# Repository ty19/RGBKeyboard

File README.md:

# RGBKeyboard
Custom RGB Keyboard PCB and Firmware project

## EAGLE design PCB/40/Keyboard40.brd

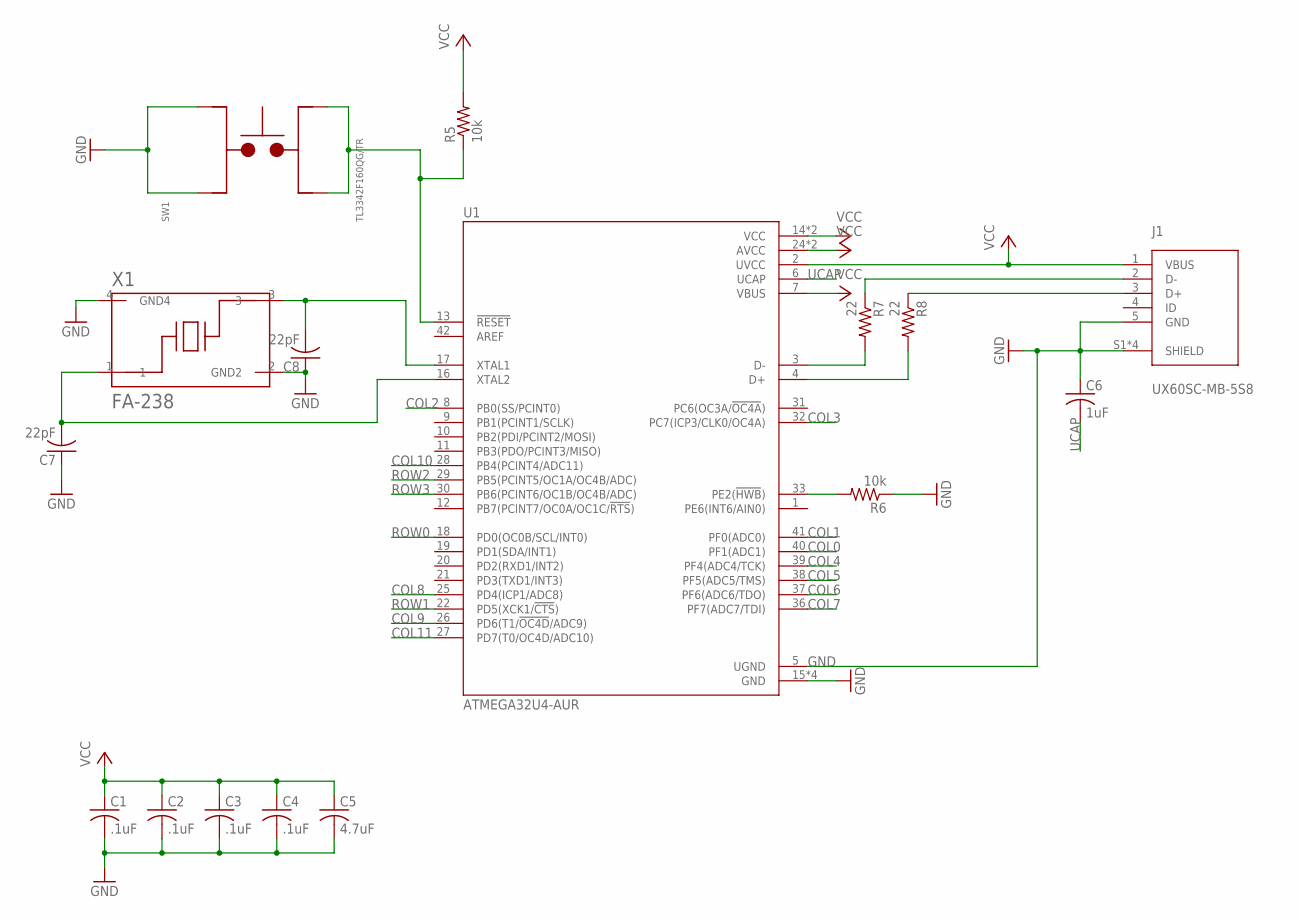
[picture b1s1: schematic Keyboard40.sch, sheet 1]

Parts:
C1, C2, C3, C4: .1uF; C0805
C5: 4.7uF; C0805
C6: 1uF; C0805
C7, C8: 22pF; C0805
J1: UX60SC-MB-5S8; HIROSE_UX60SC-MB-5S8
R5, R6: 10k; R0805
R7, R8: 22; R0805
SW1: TL3342F160QG/TR; SW_TL3342F160QG/TR
U1: ATMEGA32U4-AUR; QFP80P1200X1200X120-44N
X1: FA-238; OSCCC320X250X70-4N

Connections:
COL0: U1.40 (PF1(ADC1)); also elsewhere on the board
COL1: U1.41 (PF0(ADC0)); also elsewhere on the board
COL2: U1.8 (PB0(SS/PCINT0)); also elsewhere on the board
COL3: U1.32 (PC7(ICP3/CLK0/OC4A)); also elsewhere on the board
COL4: U1.39 (PF4(ADC4/TCK)); also elsewhere on the board
COL5: U1.38 (PF5(ADC5/TMS)); also elsewhere on the board
COL6: U1.37 (PF6(ADC6/TDO)); also elsewhere on the board
COL7: U1.36 (PF7(ADC7/TDI)); also elsewhere on the board
COL8: U1.25 (PD4(ICP1/ADC8)); also elsewhere on the board
COL9: U1.26 (PD6(T1/!OC4D!/ADC9)); also elsewhere on the board
COL10: U1.28 (PB4(PCINT4/ADC11)); also elsewhere on the board
COL11: U1.27 (PD7(T0/OC4D/ADC10)); also elsewhere on the board
GND: C1.2, C2.2, C3.2, C4.2, C5.2, C6.1, C7.1, C8.1, J1.5 (GND), J1.S1 (SHIELD), J1.S2 (SHIELD), J1.S3 (SHIELD), J1.S4 (SHIELD), R6.1, SW1.3, SW1.4, U1.5 (UGND), U1.15 (GND), U1.23 (GND), U1.35 (GND), U1.43 (GND), X1.2 (GND2), X1.4 (GND4)
unnamed: C8.2, U1.17 (XTAL1), X1.3
unnamed: C7.2, U1.16 (XTAL2), X1.1
unnamed: R5.1, SW1.1, SW1.2, U1.13 (!RESET)
unnamed: R6.2, U1.33 (PE2(!HWB!))
unnamed: R7.2, U1.3 (D-)
unnamed: J1.2 (D-), R7.1
unnamed: R8.2, U1.4 (D+)
unnamed: J1.3 (D+), R8.1
ROW0: U1.18 (PD0(OC0B/SCL/INT0)); also elsewhere on the board
ROW1: U1.22 (PD5(XCK1/!CTS!)); also elsewhere on the board
ROW2: U1.29 (PB5(PCINT5/OC1A/OC4B/ADC)); also elsewhere on the board
ROW3: U1.30 (PB6(PCINT6/OC1B/OC4B/ADC)); also elsewhere on the board
UCAP: C6.2, U1.6 (UCAP)
VCC: C1.1, C2.1, C3.1, C4.1, C5.1, J1.1 (VBUS), R5.2, U1.2 (UVCC), U1.7 (VBUS), U1.14 (VCC), U1.24 (AVCC), U1.34 (VCC), U1.44 (AVCC)

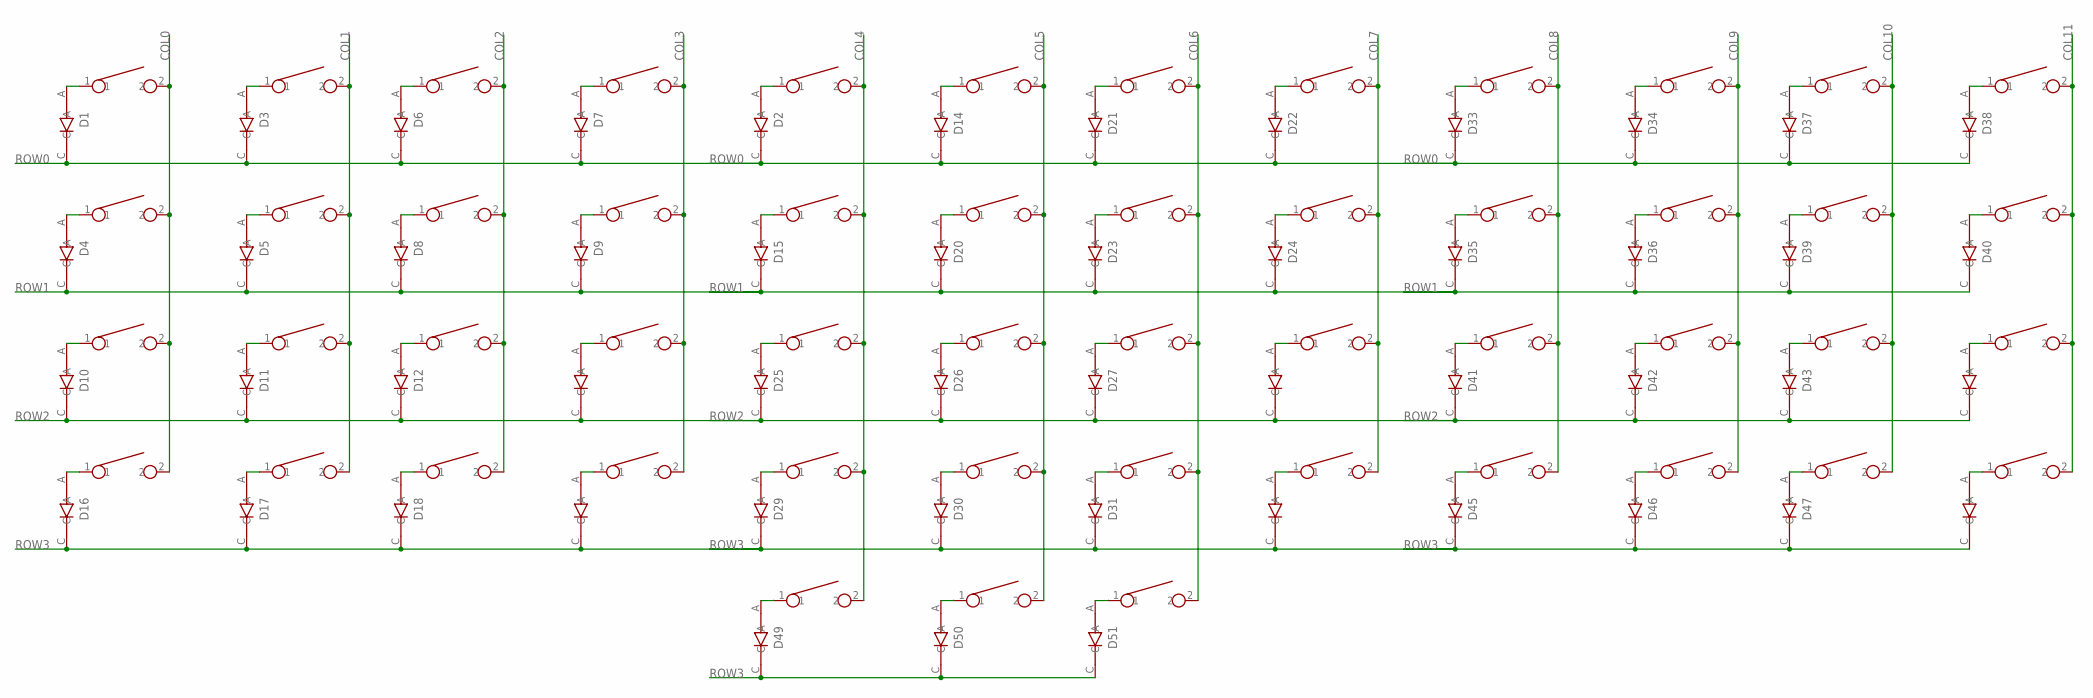
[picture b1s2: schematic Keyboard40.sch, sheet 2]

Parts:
D1, D2, D3, D4, D5, D6, D7, D8, D9, D10, D11, D12, D13, D14, D15, D16, D17, D18, D19, D20, D21, D22, D23, D24, D25, D26, D27, D28, D29, D30, D31, D32, D33, D34, D35, D36, D37, D38, D39, D40, D41, D42, D43, D44, D45, D46, D47, D48, D49, D50, D51: BAV21W-7-F; SOD3715X135N
U$1, U$2, U$3, U$4, U$5, U$6, U$7, U$8, U$9, U$10, U$11, U$12, U$16, U$17, U$18, U$19, U$20, U$21, U$22, U$23, U$24, U$25, U$26, U$27, U$28, U$29, U$30, U$31, U$32, U$33, U$34, U$35, U$36, U$37, U$38, U$39, U$40, U$41, U$42, U$43, U$44, U$45, U$46, U$47, U$48, U$49, U$50, U$51: CHERRY_MXCHERRY_MX_PLATE; CHERRY_MX_PLATE
U$13, U$14, U$15: CHERRY_MXCHERRY_MX_1_2_PLATE; CHERRY_MX_1_2_PLATE

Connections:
COL0: U$1.2, U$2.2, U$3.2, U$17.2; also elsewhere on the board
COL1: U$4.2, U$5.2, U$6.2, U$18.2; also elsewhere on the board
COL2: U$7.2, U$8.2, U$9.2, U$19.2; also elsewhere on the board
COL3: U$10.2, U$11.2, U$12.2, U$16.2; also elsewhere on the board
COL4: U$13.2, U$22.2, U$23.2, U$24.2, U$36.2; also elsewhere on the board
COL5: U$14.2, U$25.2, U$26.2, U$27.2, U$37.2; also elsewhere on the board
COL6: U$15.2, U$28.2, U$29.2, U$30.2, U$38.2; also elsewhere on the board
COL7: U$20.2, U$21.2, U$31.2, U$35.2; also elsewhere on the board
COL8: U$34.2, U$39.2, U$40.2, U$49.2; also elsewhere on the board
COL9: U$41.2, U$42.2, U$43.2, U$50.2; also elsewhere on the board
COL10: U$44.2, U$45.2, U$46.2, U$51.2; also elsewhere on the board
COL11: U$32.2, U$33.2, U$47.2, U$48.2; also elsewhere on the board
unnamed: D9.A, U$10.1
unnamed: D5.A, U$5.1
unnamed: D7.A, U$12.1
unnamed: D20.A, U$26.1
unnamed: D14.A, U$25.1
unnamed: D3.A, U$4.1
unnamed: D11.A, U$6.1
unnamed: D13.A, U$11.1
unnamed: D16.A, U$17.1
unnamed: D19.A, U$16.1
unnamed: D49.A, U$13.1
unnamed: D17.A, U$18.1
unnamed: D24.A, U$20.1
unnamed: D22.A, U$31.1
unnamed: D26.A, U$27.1
unnamed: D28.A, U$21.1
unnamed: D25.A, U$24.1
unnamed: D2.A, U$22.1
unnamed: D15.A, U$23.1
unnamed: D21.A, U$28.1
unnamed: D23.A, U$29.1
unnamed: D27.A, U$30.1
unnamed: D36.A, U$42.1
unnamed: D6.A, U$7.1
unnamed: D32.A, U$35.1
unnamed: D8.A, U$8.1
unnamed: D12.A, U$9.1
unnamed: D10.A, U$3.1
unnamed: D1.A, U$1.1
unnamed: D4.A, U$2.1
unnamed: D30.A, U$37.1
unnamed: D31.A, U$38.1
unnamed: D29.A, U$36.1
unnamed: D34.A, U$41.1
unnamed: D40.A, U$32.1
unnamed: D38.A, U$47.1
unnamed: D42.A, U$43.1
unnamed: D44.A, U$33.1
unnamed: D41.A, U$40.1
unnamed: D33.A, U$34.1
unnamed: D35.A, U$39.1
unnamed: D37.A, U$44.1
unnamed: D39.A, U$45.1
unnamed: D43.A, U$46.1
unnamed: D48.A, U$48.1
unnamed: D47.A, U$51.1
unnamed: D45.A, U$49.1
unnamed: D46.A, U$50.1
unnamed: D18.A, U$19.1
unnamed: D50.A, U$14.1
unnamed: D51.A, U$15.1
ROW0: D1.C, D2.C, D3.C, D6.C, D7.C, D14.C, D21.C, D22.C, D33.C, D34.C, D37.C, D38.C; also elsewhere on the board
ROW1: D4.C, D5.C, D8.C, D9.C, D15.C, D20.C, D23.C, D24.C, D35.C, D36.C, D39.C, D40.C; also elsewhere on the board
ROW2: D10.C, D11.C, D12.C, D13.C, D25.C, D26.C, D27.C, D28.C, D41.C, D42.C, D43.C, D44.C; also elsewhere on the board
ROW3: D16.C, D17.C, D18.C, D19.C, D29.C, D30.C, D31.C, D32.C, D45.C, D46.C, D47.C, D48.C, D49.C, D50.C, D51.C; also elsewhere on the board

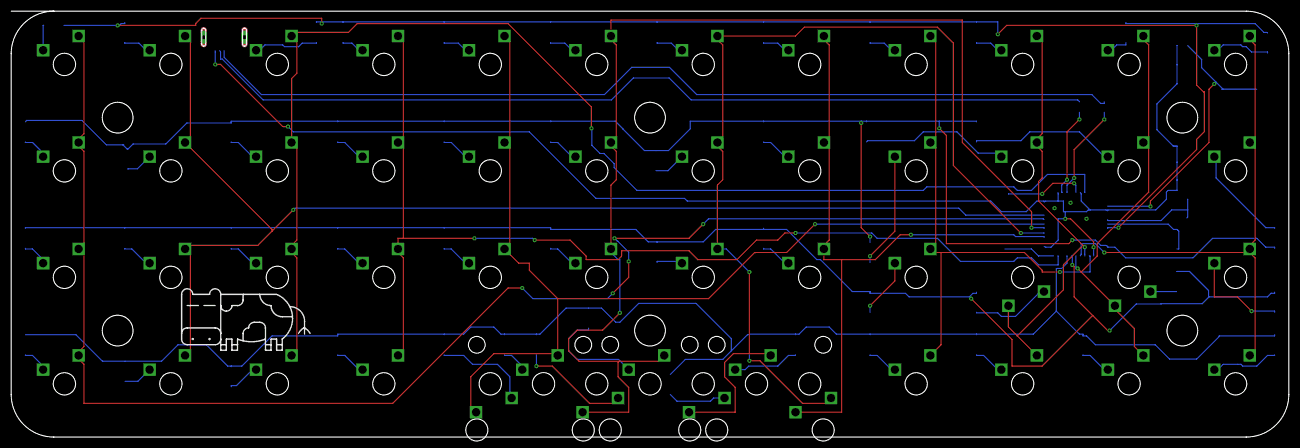
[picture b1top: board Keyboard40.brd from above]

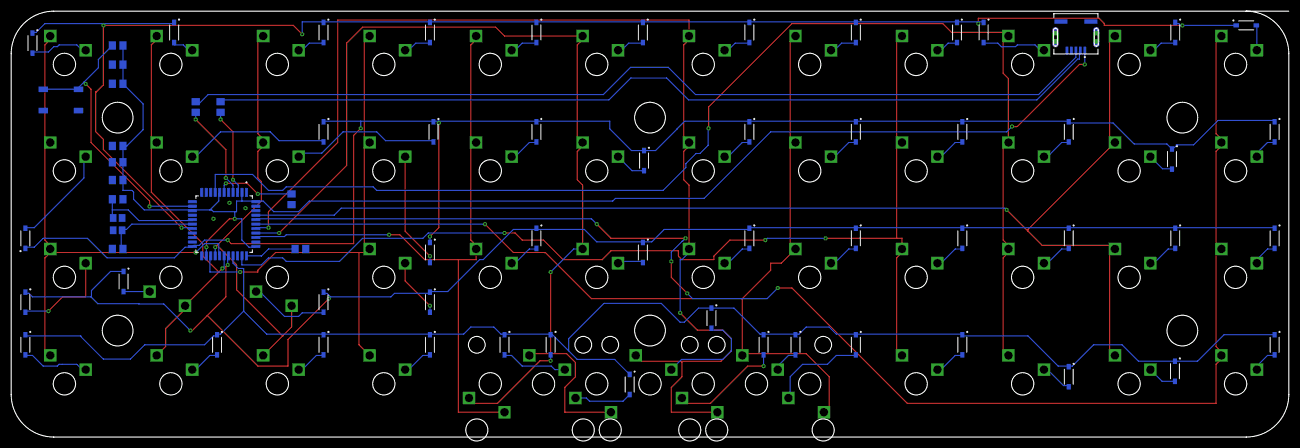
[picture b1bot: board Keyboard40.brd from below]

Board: 2 copper layers, 228.6 x 76.2 mm, 118 parts (67 on the bottom side), 78 nets.

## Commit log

2019-07-10 Initial board file
2019-07-10 MSP430F5529 and Cherry MX Switch libs
2019-07-11 USB lib and schematic
2019-07-11 Switches with LEDs and diodes
2019-07-12 Add holes for 2u and 6u led switches.
2019-07-12 Double check power and add headers
    Power is sourced from USB through VBUS, goes through
    internal LDO to VUSB and goes to DVCC.
    Headers are for row/col debug and Spi-By-Wire
2019-07-13 Add power debug pins and double check connections
2019-07-13 Temp board and schematic (commit for progress)
    Will be switching to a simpler design using the MSP430F5529
    launchpad because the tools I have right now make it hard to
    solder the MSP430 onto the board. Instead, the launchpad will
    be connected to the board using header pins.
2019-07-13 Have a decent prototype but may switch LEDs
    WS2812-2020s seem easier to solder but are harder to control.
2019-07-13 Fix stabilizer spacing for large keys
2019-07-13 Schematic and Board for first prototype
    Ended up removing the LEDs entirely (rip) because
    there was too much uncertainty with dimensions
    and routing was annoying
2019-07-14 Add Bill of Materials
2019-07-14 Shrink board to < 100 mm x 100 mm
    PCB Manufacturers (e.g. Seeed Studio) offer very cheap (~$5) prototype
    PCBs that are under 100 mm x 100 mm, after which the costs increase
2019-07-14 Further reduce size by changing spacing
2019-10-23 Minor cleanup
2019-10-25 New board design for 16 percent
2019-10-29 Make holes smaller. 19mm key spacing
2019-11-16 Create 40% layout
2019-11-16 Output files for 40
2019-11-16 Cleanup. Add holes and use plate switches
2019-11-16 Increase hole tolerance and round edges
2019-12-18 VUSB to VCC. Fix USB position
2020-02-28 Holes for new case
